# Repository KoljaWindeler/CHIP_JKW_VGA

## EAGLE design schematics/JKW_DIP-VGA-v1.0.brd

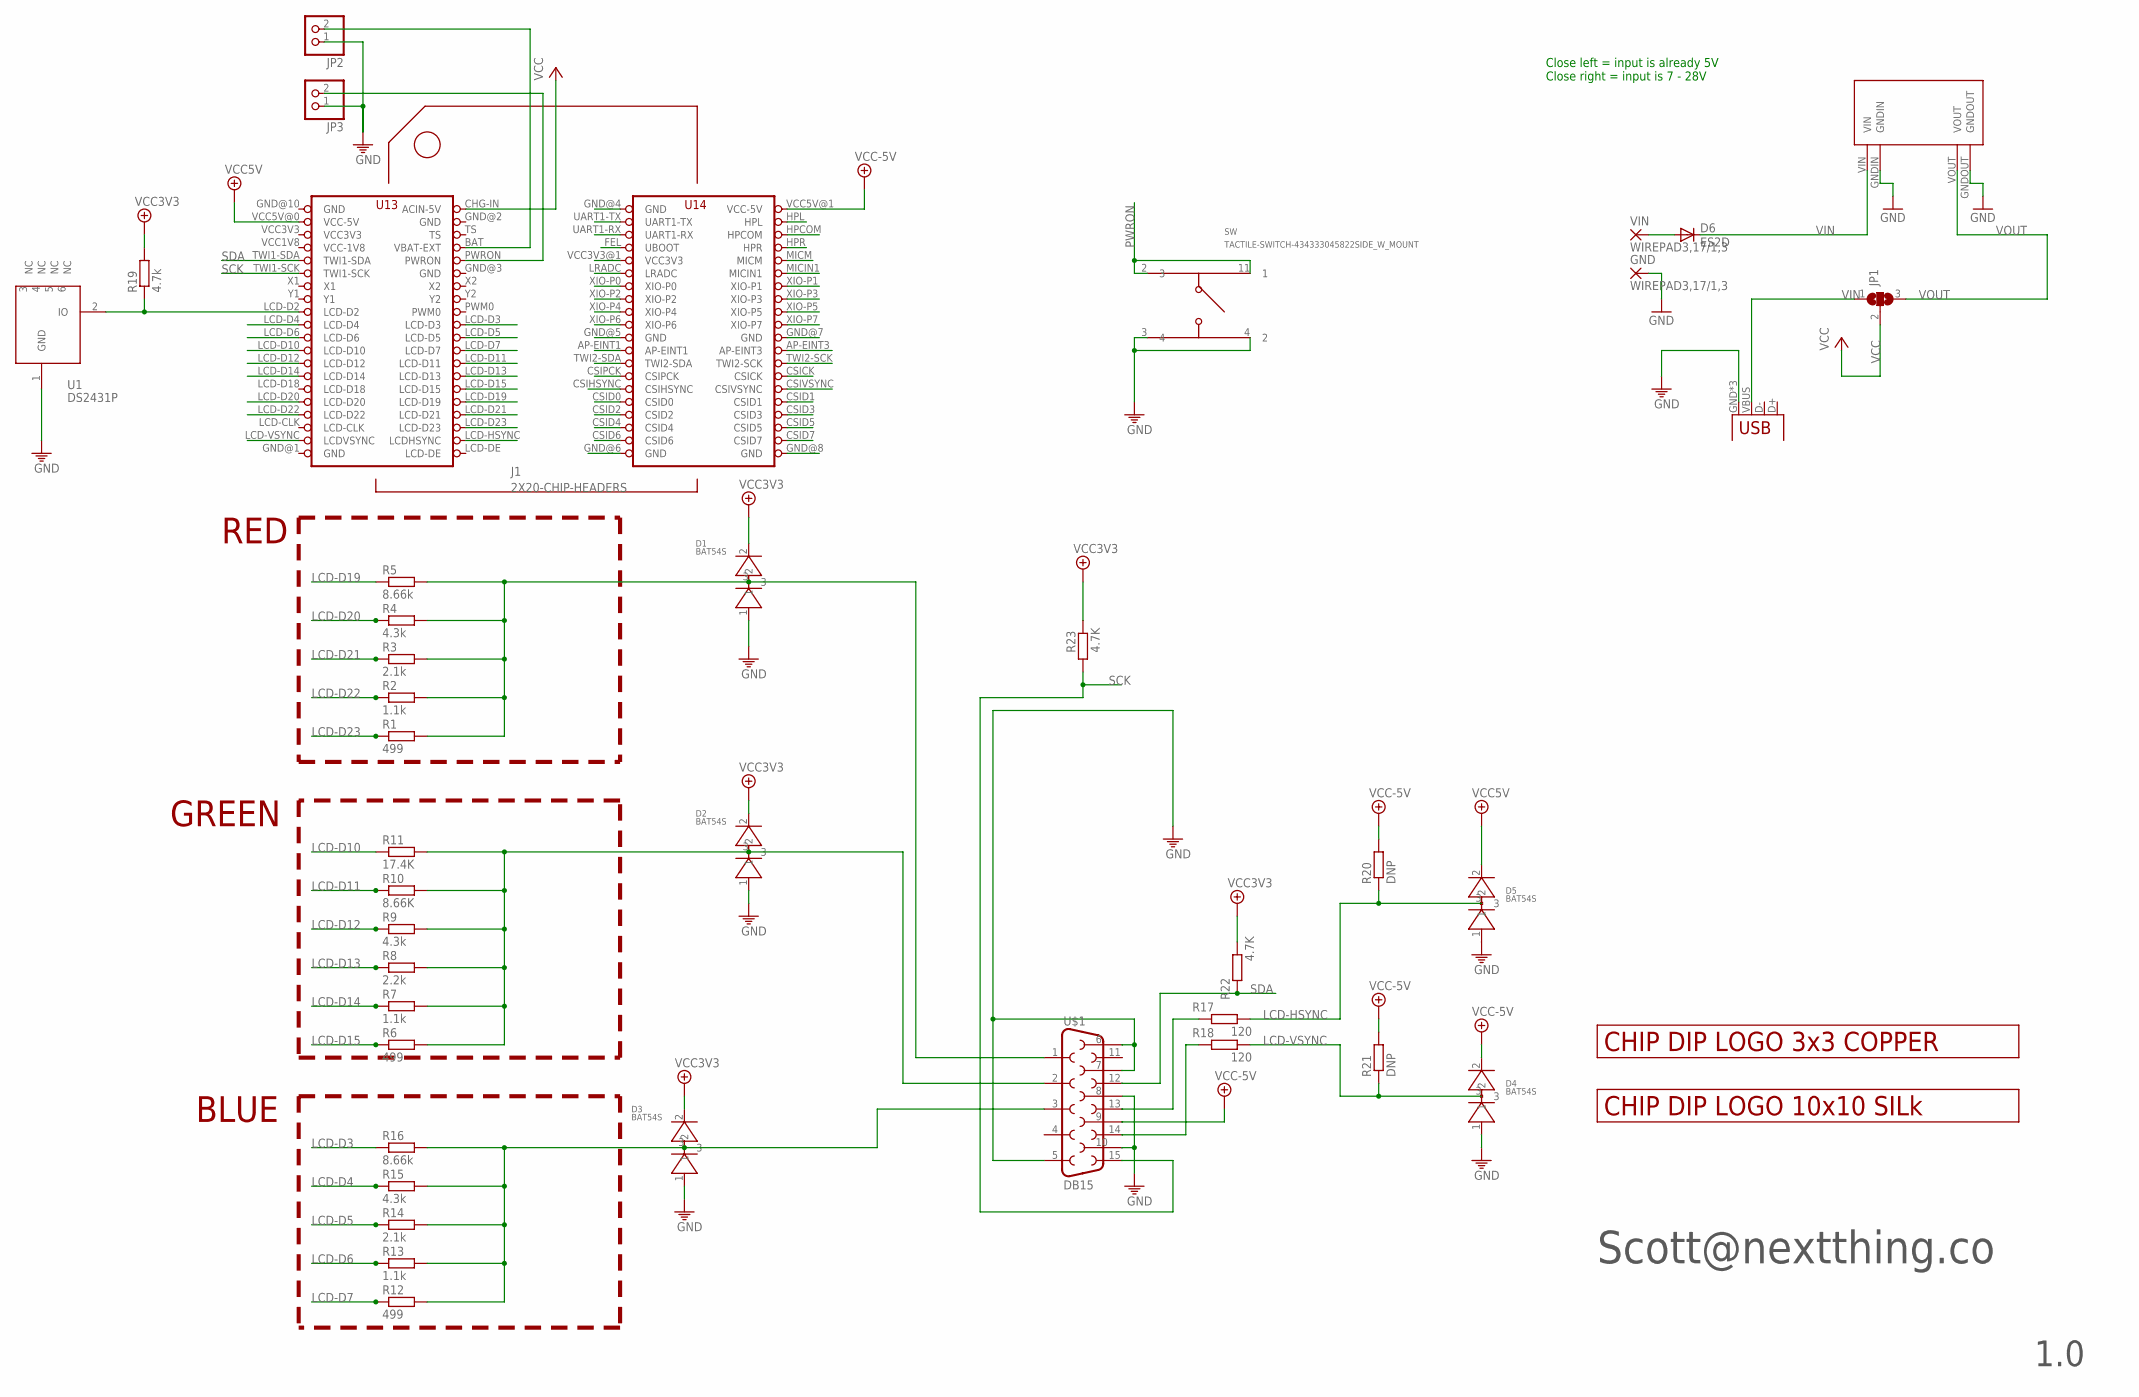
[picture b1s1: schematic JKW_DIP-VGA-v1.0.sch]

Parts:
D1, D2, D3, D4, D5: BAT54S; SOT23-BEC
D6: ES2D; SMB
GND: WIREPAD3,17/1,3; 3,17/1,3
J1: 2X20-CHIP-HEADERS; 2X20CHIP_SM
JP1: SJ2W; SJ_2
JP2, JP3: PINHD-1X2; 1X02
R1, R6, R12: 499; R0805
R2, R7, R13: 1.1k; R0805
R3, R14: 2.1k; R0805
R4, R9, R15: 4.3k; R0805
R5, R16: 8.66k; R0805
R8: 2.2k; R0805
R10: 8.66K; R0805
R11: 17.4K; R0805
R17, R18: 120; R0805
R19: 4.7k; R0805
R20, R21: DNP; R0805
R22, R23: 4.7K; R0805
SW: TACTILE-SWITCH-434333045822SIDE_W_MOUNT; TACTILE-SWITCH-K2-1114UA-AW
U1: DS2431P; TSOC6
U$1: DB15
U$5: LOGO_3X3_COPPER
U$6: LOGO_10X10_SILK
U$9: MP1584EN
USB: USBUSB-MICROB-SMT-DIP; USB-MICROB-SMT-DIP
VIN: WIREPAD3,17/1,3; 3,17/1,3

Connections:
1: J1.CSIVSYNC
AP-EINT1: J1.AP-EINT1
AP-EINT3: J1.AP-EINT3
BAT: J1.BAT (VBAT-EXT), JP2.2
CSICK: J1.CSICK
CSID0: J1.CSID0
CSID1: J1.CSID1
CSID2: J1.CSID2
CSID3: J1.CSID3
CSID4: J1.CSID4
CSID5: J1.CSID5
CSID6: J1.CSID6
CSID7: J1.CSID7
CSIHSYNC: J1.CSIHSYNC
CSPICK: J1.CSIPCK
FEL: J1.FEL (UBOOT)
GND: D1.1, D2.1, D3.1, D4.1, D5.1, GND.1, J1.GND@1 (GND), J1.GND@2 (GND), J1.GND@3 (GND), J1.GND@4 (GND), J1.GND@5 (GND), J1.GND@6 (GND), J1.GND@7 (GND), J1.GND@8 (GND), J1.GND@10 (GND), JP2.1, JP3.1, SW.3 (4), SW.4 (2), U1.1 (GND), U$1.5, U$1.6, U$1.7, U$1.8, U$1.10, U$9.GNDIN, U$9.GNDOUT, USB.GND, USB.MT1 (GND), USB.MT2 (GND)
HPCOM: J1.HPCOM
HPL: J1.HPL
HPR: J1.HPR
LCD-D3: J1.LCD-D3, R16.1
LCD-D4: J1.LCD-D4, R15.1
LCD-D5: J1.LCD-D5, R14.1
LCD-D6: J1.LCD-D6, R13.1
LCD-D7: J1.LCD-D7, R12.1
LCD-D10: J1.LCD-D10, R11.1
LCD-D11: J1.LCD-D11, R10.1
LCD-D12: J1.LCD-D12, R9.1
LCD-D13: J1.LCD-D13, R8.1
LCD-D14: J1.LCD-D14, R7.1
LCD-D15: J1.LCD-D15, R6.1
LCD-D19: J1.LCD-D19, R5.1
LCD-D20: J1.LCD-D20, R4.1
LCD-D21: J1.LCD-D21, R3.1
LCD-D22: J1.LCD-D22, R2.1
LCD-D23: J1.LCD-D23, R1.1
LCD-HSYNC: D5.3, J1.LCD-HSYNC (LCDHSYNC), R17.2, R20.1
LCD-VSYNC: D4.3, J1.LCD-VSYNC (LCDVSYNC), R18.2, R21.1
LRADC: J1.LRADC
MICIN1: J1.MICIN1
MICM: J1.MICM
unnamed: R17.1, U$1.13
unnamed: R18.1, U$1.14
unnamed: JP1.1, USB.VBUS
unnamed: J1.LCD-D2, R19.1, U1.2 (IO)
unnamed: D2.3, R6.2, R7.2, R8.2, R9.2, R10.2, R11.2, U$1.2
unnamed: D1.3, R1.2, R2.2, R3.2, R4.2, R5.2, U$1.1
unnamed: D3.3, R12.2, R13.2, R14.2, R15.2, R16.2, U$1.3
unnamed: D6.A, VIN.1
PWRON: J1.PWRON, JP3.2, SW.2 (3), SW.11 (1)
SCK: J1.TWI1-SCK, R23.1, U$1.15
SDA: J1.TWI1-SDA, R22.1, U$1.12
TWI2-SCK: J1.TWI2-SCK
TWI2-SDA: J1.TWI2-SDA
UART1-RX: J1.UART1-RX
UART1-TX: J1.UART1-TX
VCC: J1.CHG-IN (ACIN-5V), JP1.2
VCC3V3: D1.2, D2.2, D3.2, J1.VCC3V3, J1.VCC3V3@1 (VCC3V3), R19.2, R22.2, R23.2
VCC5V: D4.2, D5.2, J1.VCC5V@0 (VCC-5V), J1.VCC5V@1 (VCC-5V), R20.2, R21.2, U$1.9
VCC-1V8: J1.VCC1V8 (VCC-1V8)
VIN: D6.C, U$9.VIN
VOUT: JP1.3, U$9.VOUT
XIO-P0: J1.XIO-P0
XIO-P1: J1.XIO-P1
XIO-P2: J1.XIO-P2
XIO-P3: J1.XIO-P3
XIO-P4: J1.XIO-P4
XIO-P5: J1.XIO-P5
XIO-P6: J1.XIO-P6
XIO-P7: J1.XIO-P7

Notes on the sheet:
RED
GREEN
BLUE
Scott@nextthing.co
1.0
Close left = input is already 5V Close right = input is 7 - 28V

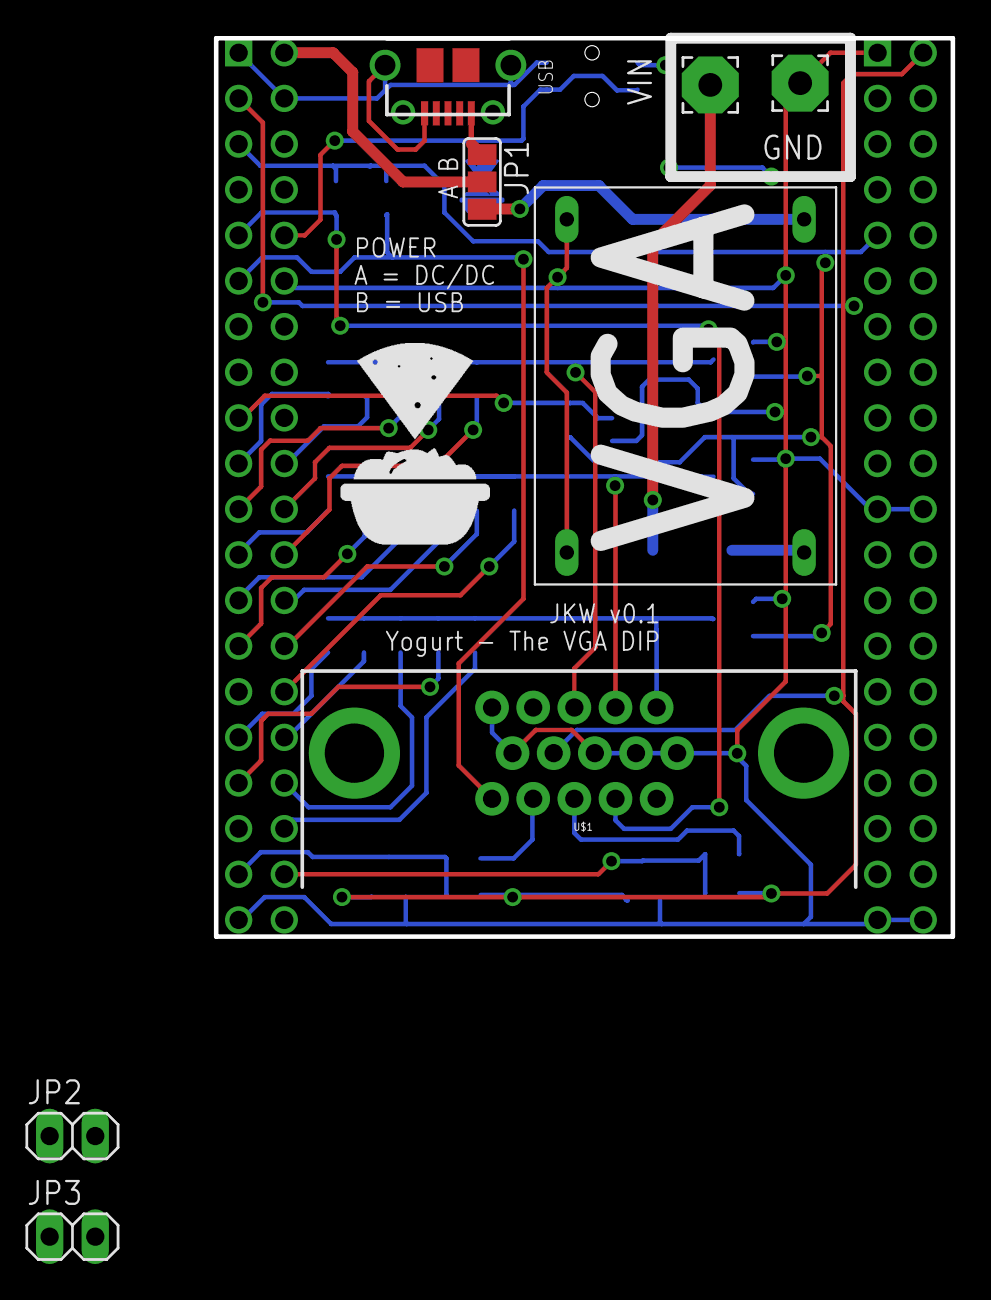
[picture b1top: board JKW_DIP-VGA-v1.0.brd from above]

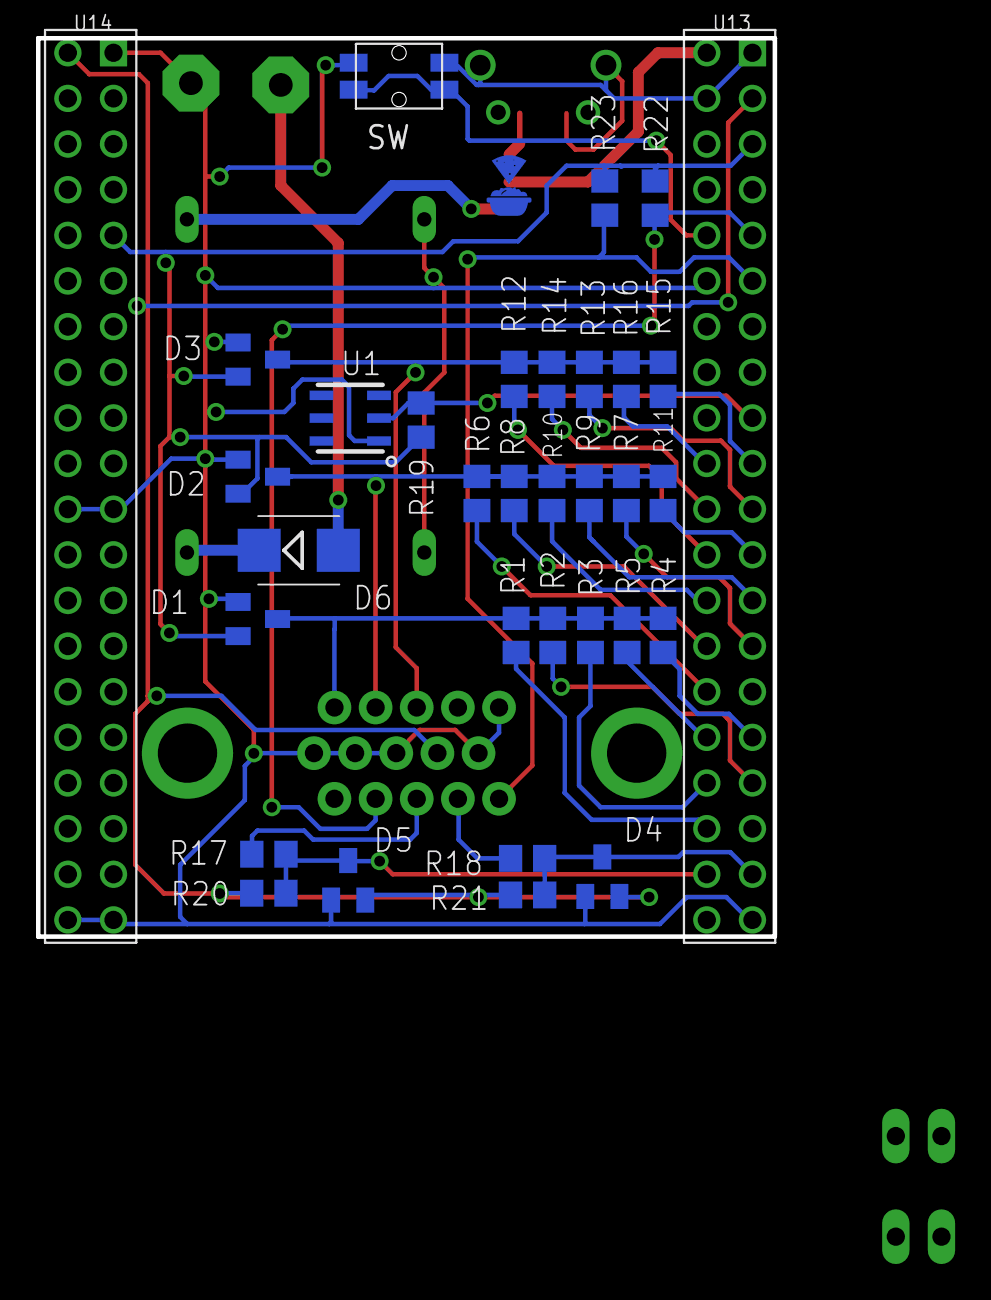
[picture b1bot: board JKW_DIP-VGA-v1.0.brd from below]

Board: 4 copper layers, 41.0 x 50.0 mm, 42 parts (32 on the bottom side), 36 nets.

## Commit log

2016-06-17 :circus_tent: Added .gitattributes & .gitignore files
2016-06-17 init
2016-06-18 ordered at elecrow
2016-07-22 moved sch to dir and added quote estimation
2016-08-20 updated VGA

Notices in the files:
parts and their libraries:
SparkFun-Connectors: Licensing: Creative Commons ShareAlike 4.0 International - https://creativecommons.org/licenses/by-sa/4.0
